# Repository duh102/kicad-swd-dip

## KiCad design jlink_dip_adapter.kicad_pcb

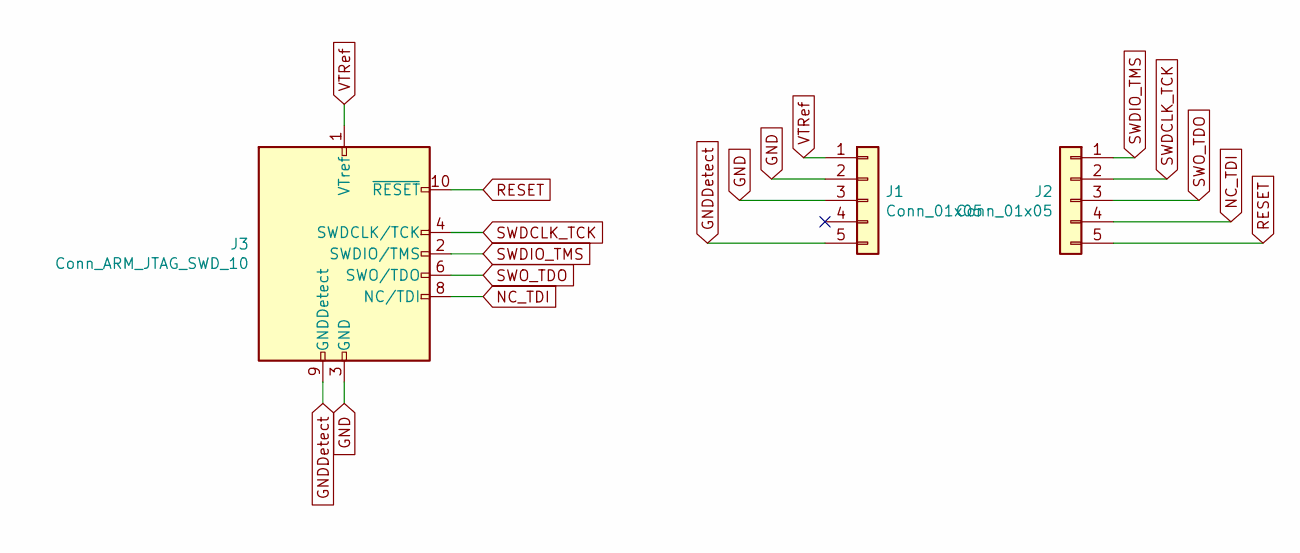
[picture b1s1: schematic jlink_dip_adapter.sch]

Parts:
J1, J2: Conn_01x05; PinHeader_1x05_P2.54mm_Vertical
J3: Conn_ARM_JTAG_SWD_10; PinHeader_2x05_P1.27mm_Vertical_SMD

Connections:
GND: J1.2, J1.3, J3.3 (GND), J3.5 (GND)
GNDDetect: J1.5, J3.9 (GNDDetect)
NC_TDI: J2.4, J3.8 (NC/TDI)
RESET: J2.5, J3.10 (~RESET~)
SWDCLK_TCK: J2.2, J3.4 (SWDCLK/TCK)
SWDIO_TMS: J2.1, J3.2 (SWDIO/TMS)
SWO_TDO: J2.3, J3.6 (SWO/TDO)
VTRef: J1.1, J3.1 (VTref)

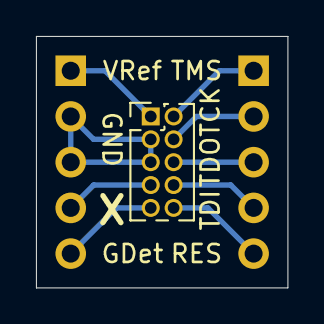
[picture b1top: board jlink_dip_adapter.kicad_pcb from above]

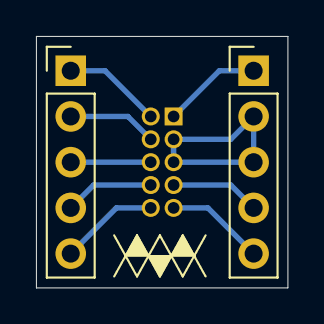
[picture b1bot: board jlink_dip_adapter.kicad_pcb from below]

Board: 2 copper layers, 14.0 x 14.0 mm, 3 parts (2 on the bottom side), 8 nets.
